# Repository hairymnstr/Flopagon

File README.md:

# Flopagon

A 16MB Flash storage solution for the [Tildagon](https://tildagon.badge.emfcamp.org/).  The Flopagon
is styled to look like a classic 3.5" floppy disk but it is functional as well.

## Hardware

### Schematic

There's a PDF of the [schematic](flopagon.pdf)

### Manufacturing files

The files I used to get the boards made and assembled by [JLC PCB](https://jlcpcb.com) are in the `manufacturing/version 1` folder.
The part numbers in the KiCad schematic reference parts from JLC/LCSC which can be used for their assembly service.

### Description

The Flopagon has two chips on it:

#### The EEPROM

There's a small (2kB) EEPROM in line with the [Hexpansion specification](https://tildagon.badge.emfcamp.org/hexpansions/creating-hexpansions/),
this is write protected by default and is designed to have an identity and a small helper app to get the Flopagon up and running.

To write the EEPROM you need to short the two pads of the unpopulated 0.1" header in the corner of the Flopagon.  You can do that easily with a
bit of wire, a pair of tweezers etc.

Flopagon V2 (you can tell it's a V2 because it's black not blue) has an 8kB EEPROM
for a bit of extra space.

#### The Flash Memory

The second chip is a 16MB Flash chip, this connects via an SPI interface using the 4 high-speed I/O pins on the hexpansion interface.
This chip can be formatted with a filesystem and used for storing Python scripts or images, music, data files etc.

## Software

The EEPROM on the Flopagon can be programmed with a simple app that lets you
mount/unmount and format the storage.  Source is in the `app` directory.  To squeeze
the code into the small EEPROM on the original Flopagon it needs to be compiled to
a `*.mpy` file, I've done this already but if you want to modify it you'll need to
do this step.  You need the [mpy-cross](https://pypi.org/project/mpy-cross/) tool
then you can simply run

    mpy-cross app.py

To setup a Flopagon you need to plug it in to your badge and connect to the badge using [mpremote]().  The Tildagon on-board Hexpansion manager will be able to do
this for you soon, but for development reasons you'll still need to follow the steps

On the host change into the `app` directory of a checkout of this repository and run:

    mpremote mount .

This will connect to the running micropython system on your badge, hit `Ctrl-C` to
interrupt the normal OS and get a Python prompt.

    from prepare_eeprom import setup_flopagon

(Obviously import setup_flopagon_v2 if you've got one of the new black ones.  The
only difference is the size of the EEPROM in the header)

Fit the flopagon into a port, they're numbered from 1 clockwise from the top/right 
port.  Short the write-protect jumper, I normally stuff a pair of tweezers in the 
holes.  Now run the command:

    setup_flopagon(2)

The port number needs to be passed, in this example I've used port 2 (right hand
side).  That should do all the formatting and mount and copy the app onto the EEPROM.

Reset the badge to get the hexpansion to do its thing.  It should pop up an app
that lets you mount or format the hexpansion.

## Ideas I've had for using a flopagon

I think with the right code it should be possible to automatically start the Flash chip using a small program on the EEPROM.  From there
you could start launching code from the mounted filesystem so you could have a game that starts when you plug in the Flopagon, like a
cartridge.

Perhaps a file manager app for the badge is required?

Maybe you could put [Doom](https://github.com/espressif/esp32-doom) on a Flopagon?

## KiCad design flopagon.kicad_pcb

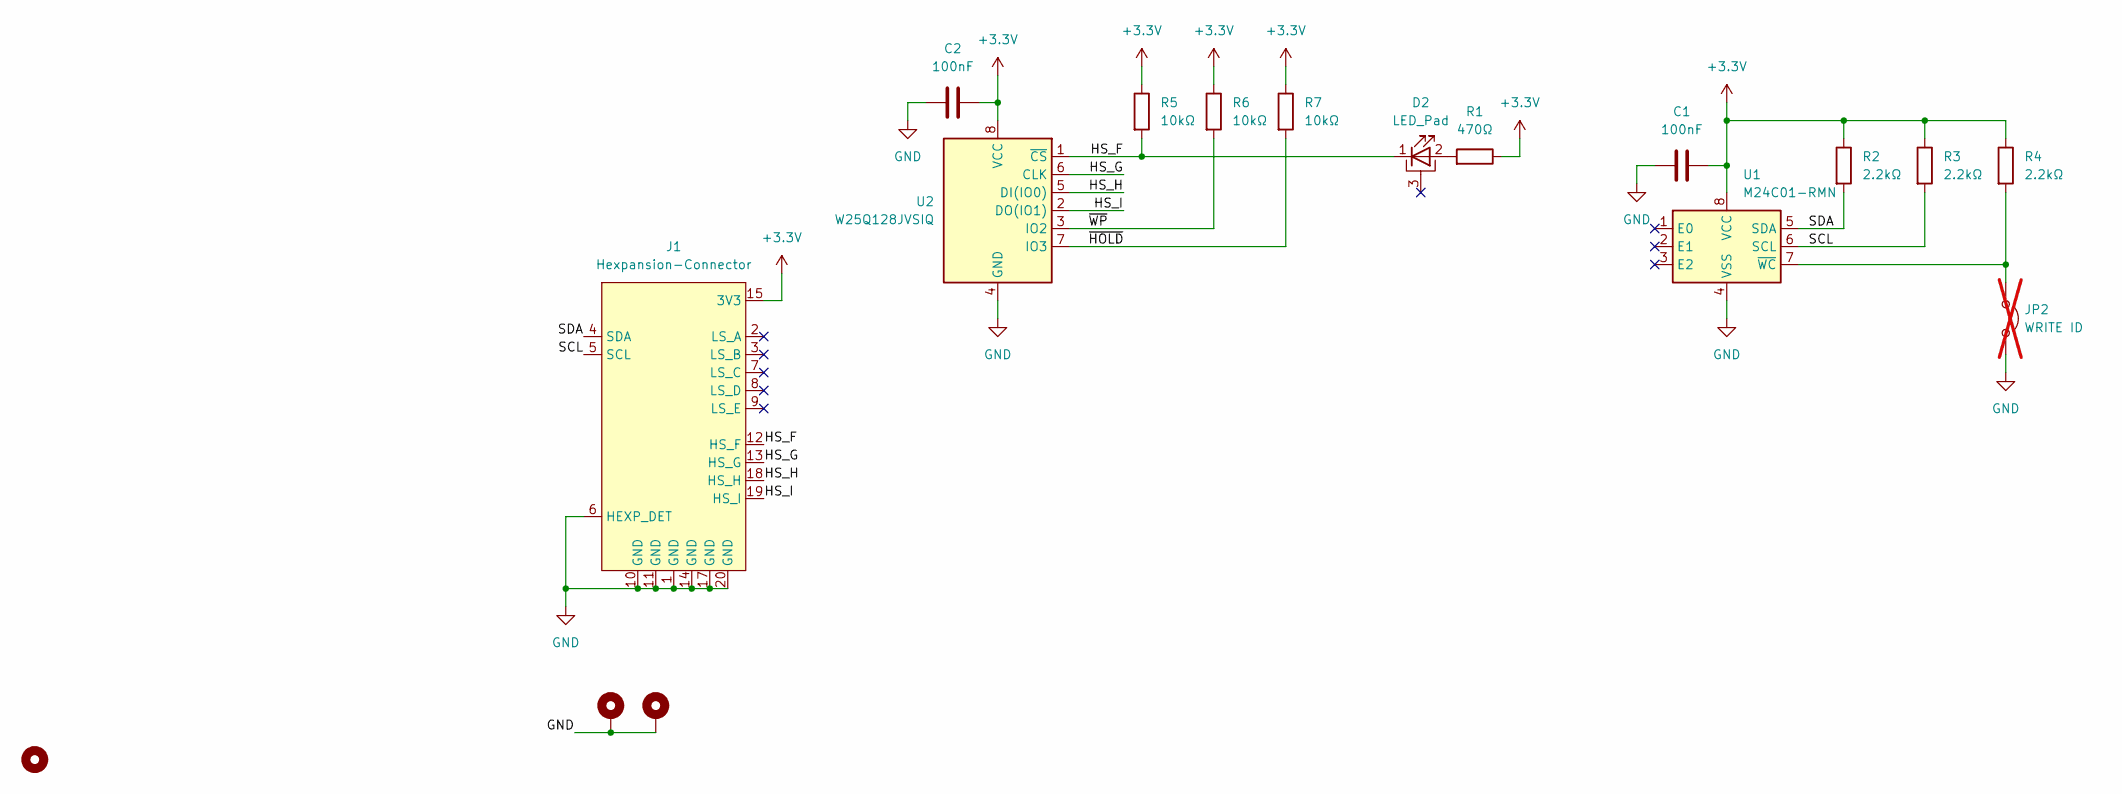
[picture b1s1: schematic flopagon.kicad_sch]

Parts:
C1, C2: 100nF; C_0603_1608Metric; LCSC C14663
D2: LED_Pad; LED_1204_Sideview; LCSC C5160726
H1, H2: MountingHole_Pad; MountingHole_2.2mm_M2_Pad_Via
H3: MountingHole; floppy_12mm
J1: Hexpansion-Connector; hexpansion-edge-connector
JP2: WRITE ID; PinHeader_1x02_P2.54mm_Vertical; not fitted
R1: 470Ω; R_0603_1608Metric; LCSC C23179
R2, R3, R4: 2.2kΩ; R_0603_1608Metric; LCSC C4190
R5, R6, R7: 10kΩ; R_0603_1608Metric; LCSC C25804
U1: M24C01-RMN; SOIC-8_3.9x4.9mm_P1.27mm; LCSC C79946
U2: W25Q128JVSIQ; SOIC-8_5.23x5.23mm_P1.27mm; LCSC C97521

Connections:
+3.3V: C1.2, C2.2, J1.15 (3V3), J1.16 (3V3), R1.1, R2.1, R3.1, R4.1, R5.1, R6.1, R7.1, U1.8 (VCC), U2.8 (VCC)
/HS_F: D2.1 (K), J1.12 (HS_F), R5.2, U2.1 (~CS)
/HS_G: J1.13 (HS_G), U2.6 (CLK)
/HS_H: J1.18 (HS_H), U2.5 (DI(IO0))
/HS_I: J1.19 (HS_I), U2.2 (DO(IO1))
/SCL: J1.5 (SCL), R3.2, U1.6 (SCL)
/SDA: J1.4 (SDA), R2.2, U1.5 (SDA)
/~HOLD: R7.2, U2.7 (IO3)
/~WP: R6.2, U2.3 (IO2)
GND: C1.1, C2.1, H1.1, H2.1, J1.1 (GND), J1.6 (HEXP_DET), J1.10 (GND), J1.11 (GND), J1.14 (GND), J1.17 (GND), J1.20 (GND), JP2.2 (B), U1.4 (VSS), U2.4 (GND)
unnamed: D2.2 (A), R1.2
unnamed: JP2.1 (A), R4.2, U1.7 (~WC)

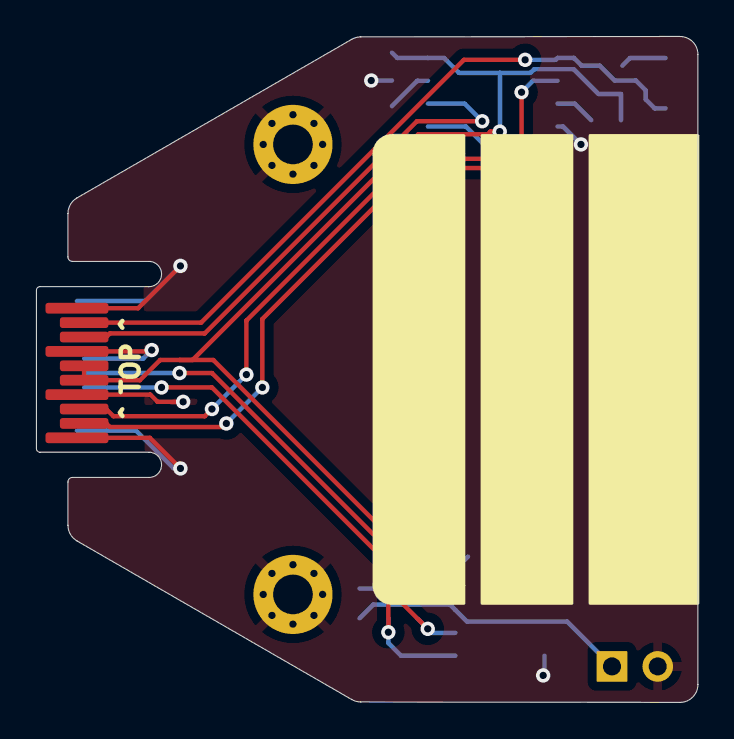
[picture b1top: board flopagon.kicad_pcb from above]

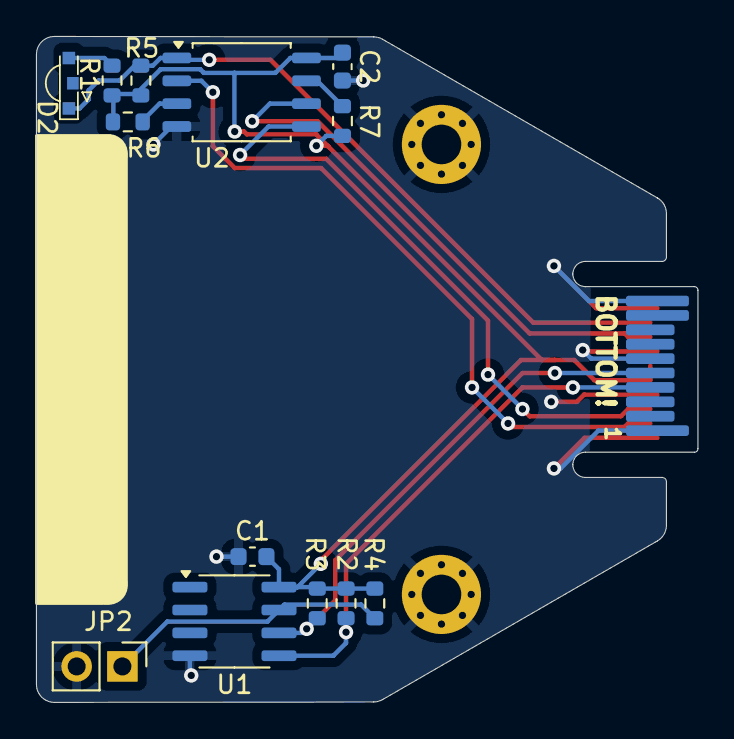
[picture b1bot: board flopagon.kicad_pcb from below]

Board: 2 copper layers, 36.8 x 37.0 mm, 17 parts (14 on the bottom side), 12 nets.

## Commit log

2024-06-07 Finally committing this stuff to Git
2025-03-06 Updated schematic to make the EEPROM part clearer
2026-06-08 Updates to the app to unmount cleanly
2026-06-13 Latest app version, more reliable
2026-06-14 Make README use correct function name
    v1 flopagon setup function doesn't have version number in it in the .py file
2026-06-30 Updated app to use new eventbus methods
